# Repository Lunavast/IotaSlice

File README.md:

IotaSlice
===========

Iota is my approach at a little powder based 3D printer.

IotaSlice is a crude pre-alpha version of software the slices
3DS formatted 3D models into bitmap slices. Every pixel then
corresponds to the ink fired from a nozzle of the 3D printer.

The Iota firmware includes a minimal interpreter that reads
files in a propritary language from SD card and creates the
appropriate signals for all steppers and the ink shield output
of the Iota machine, much like G-Code in the early days of
CNC machines.

Iota Slice uses OpenGL to create 2D surfaces out of 3D shapes.
Slices have a real height. They are not just 2D cuts through
the model, but real 3D slices of a give thinkness, projected
onto a 2D surface. This method may capture fine details that
may otherwise be lost.

Iota Slice has some crude ideas of a shell, creating different
ink densities around the model as opposed to the inside. There
are some first hooks to implement vertex-based color 
gradiations, but the 3DS interface is not yet implemented.
The next version will implement full color based on texture 
mapping.

Also, at some point, the entire code will have to be 
reorganized and cleaned and wrapped into a nice UI. Until
then, this code is purely educational for the brave.

 Matthias

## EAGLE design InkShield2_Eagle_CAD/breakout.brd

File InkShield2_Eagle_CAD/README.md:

InkShield2
============

This board has been tested. It works quite well.

Periperials required are Polulo stepper drivers for
X, Y, Z1, and Z2, four endstops (optical gates),
an HP ink head, and a four-line I2C display with
four push buttons for menu selection.

Power supply is via a regular PC power brick
that is siply plugged into the shield. The voltage
needed for the Arduino Mega, all steppers, the SD
card connector, and the Ink Head are all taken 
from or generated from the PC power supply.

This is my original setup:

 https://www.youtube.com/watch?v=zV6xfxpeGGE

 Matthias

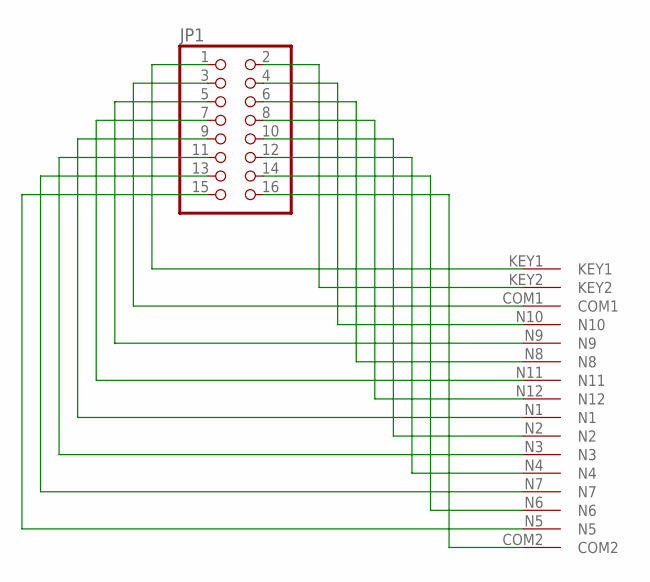
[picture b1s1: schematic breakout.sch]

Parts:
JP1: PINHD-2X8; 2X08
U$1: CON_16X1

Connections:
unnamed: JP1.1, U$1.KEY1
unnamed: JP1.2, U$1.KEY2
unnamed: JP1.3, U$1.COM1
unnamed: JP1.4, U$1.N10
unnamed: JP1.5, U$1.N9
unnamed: JP1.6, U$1.N8
unnamed: JP1.7, U$1.N11
unnamed: JP1.8, U$1.N12
unnamed: JP1.9, U$1.N1
unnamed: JP1.10, U$1.N2
unnamed: JP1.11, U$1.N3
unnamed: JP1.12, U$1.N4
unnamed: JP1.13, U$1.N7
unnamed: JP1.14, U$1.N6
unnamed: JP1.15, U$1.N5
unnamed: JP1.16, U$1.COM2

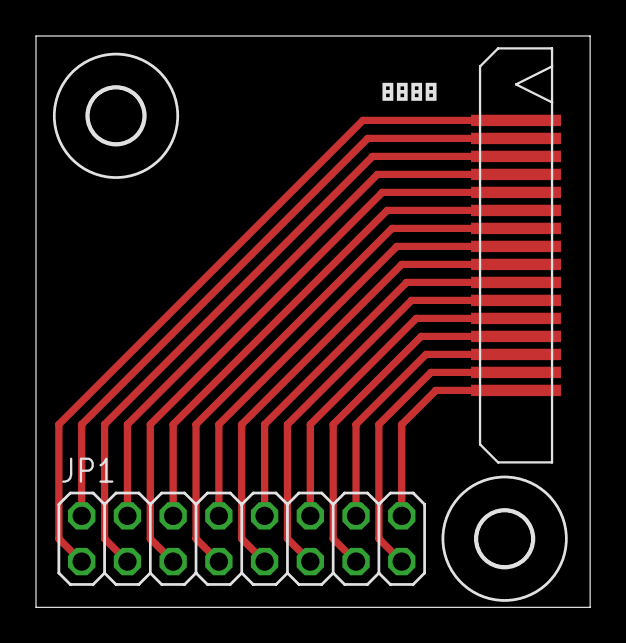
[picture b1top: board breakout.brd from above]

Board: 2 copper layers, 30.8 x 31.7 mm, 5 parts (0 on the bottom side), 16 nets.

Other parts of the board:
U$2: LP_NUMBER_SILK_TOP
U$3, U$4: 3,0

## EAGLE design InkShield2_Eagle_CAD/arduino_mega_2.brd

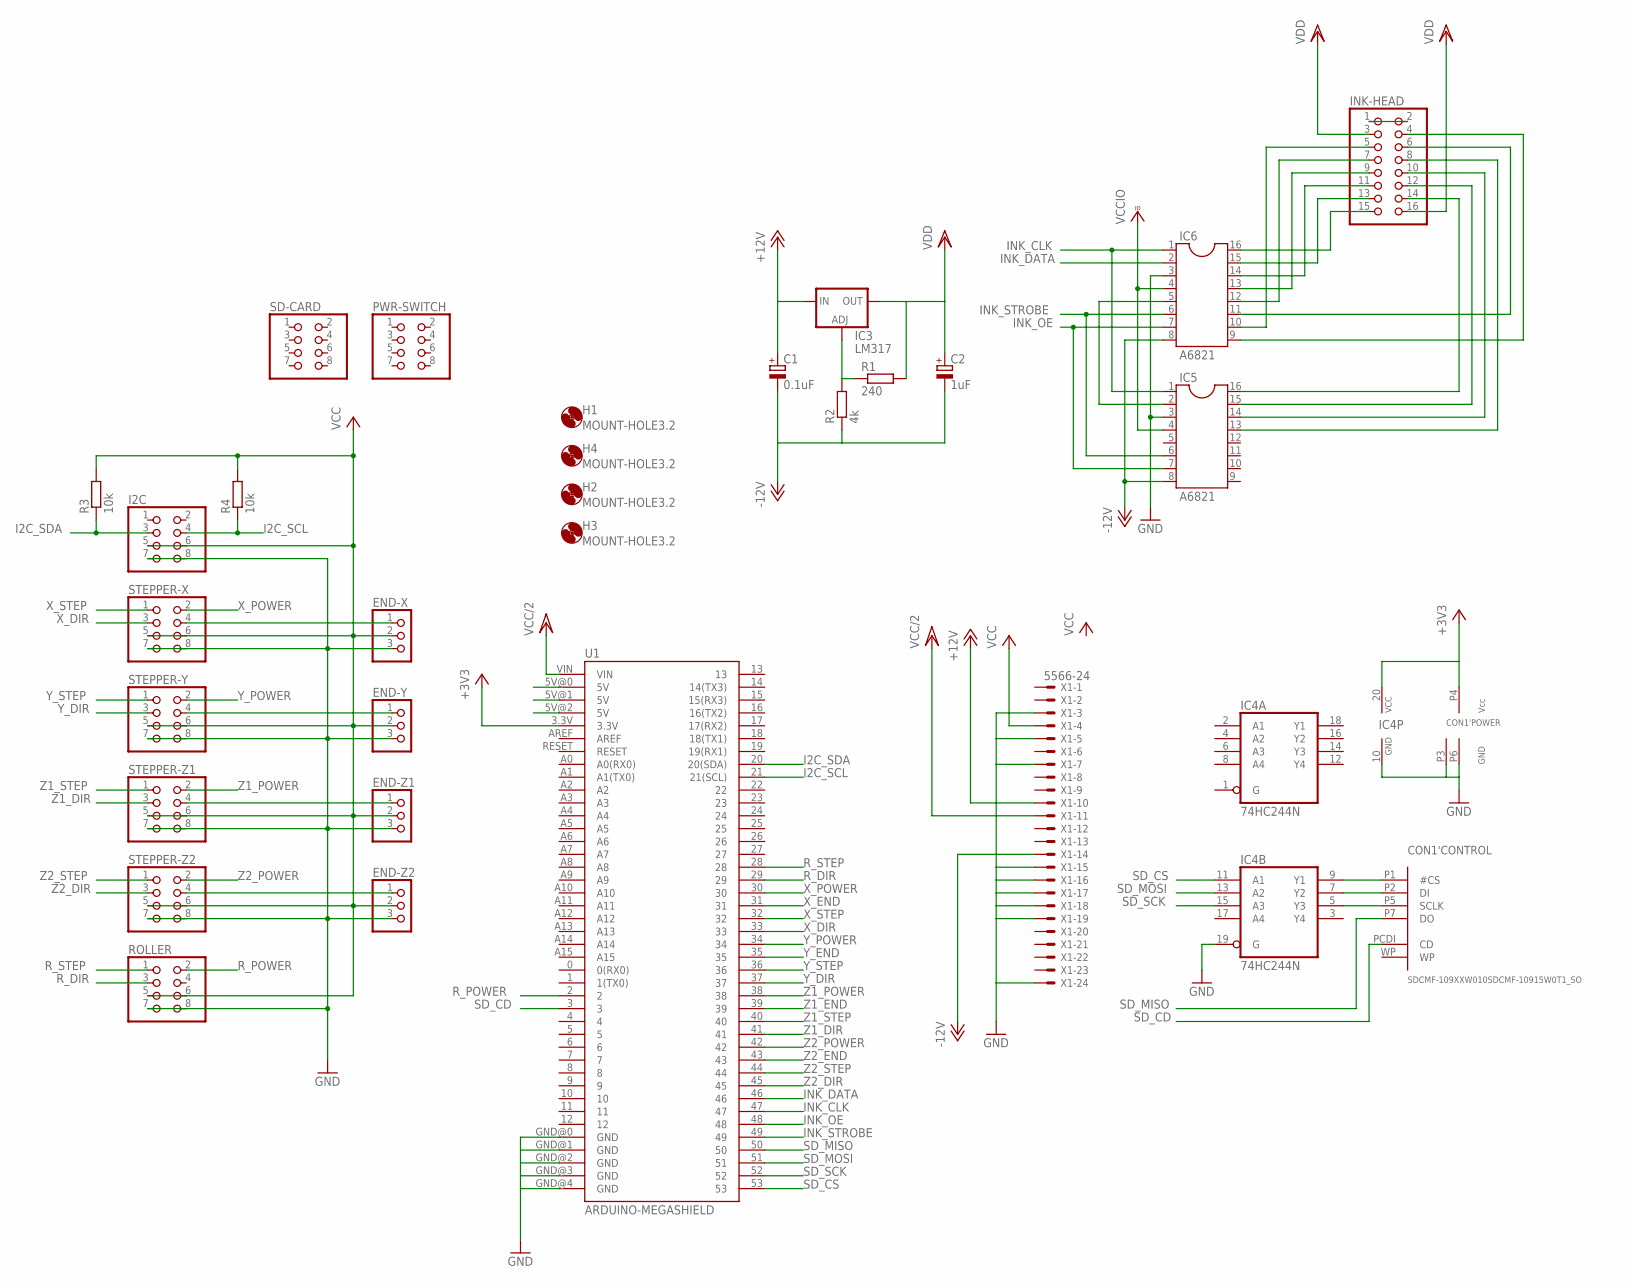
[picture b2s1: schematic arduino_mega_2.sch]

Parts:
C1: 0.1uF; E2-5
C2: 1uF; E2-5
CON1: SDCMF-109XXW010SDCMF-10915W0T1_SO; SDCMF-10915W0T1
END-X: PINHD-1X3; 1X03
END-Y: PINHD-1X3; 1X03
END-Z1, END-Z2: PINHD-1X3; 1X03
H1, H2, H3, H4: MOUNT-HOLE3.2; 3,2
I2C: PINHD-2X4; 2X04
IC3: LM317; 317TL
IC4: 74HC244N; DIL20
IC5, IC6: A6821; DIL16
INK-HEAD: PINHD-2X8; 2X08
PWR-SWITCH: PINHD-2X4; 2X04
R1: 240; 0207/10
R2: 4k; 0207/10
R3, R4: 10k; 0204/7
ROLLER: PINHD-2X4; 2X04
SD-CARD: PINHD-2X4; 2X04
STEPPER-X: PINHD-2X4; 2X04
STEPPER-Y: PINHD-2X4; 2X04
STEPPER-Z1, STEPPER-Z2: PINHD-2X4; 2X04
U1: ARDUINO-MEGASHIELD; ARDUINO_MEGA_SHIELD
X1: 5566-24

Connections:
+3V3: CON1.P4 (VCC), IC4.20 (VCC), U1.3.3V
+12V: C1.+, IC3.3 (IN), X1.10
-12V: C1.-, C2.-, IC5.8, IC6.8, R2.1, X1.14
GND: CON1.P3 (GND), CON1.P6 (GND), END-X.3, END-Y.3, END-Z1.3, END-Z2.3, I2C.7, I2C.8, IC4.10 (GND), IC4.19 (G), IC5.3, IC6.3, ROLLER.7, ROLLER.8, STEPPER-X.7, STEPPER-X.8, STEPPER-Y.7, STEPPER-Y.8, STEPPER-Z1.7, STEPPER-Z1.8, STEPPER-Z2.7, STEPPER-Z2.8, U1.GND@0 (GND), U1.GND@1 (GND), U1.GND@2 (GND), U1.GND@3 (GND), U1.GND@4 (GND), X1.3, X1.5, X1.7, X1.15, X1.16, X1.17, X1.18, X1.19, X1.24
I2C_SCL: I2C.4, R4.1, U1.21 (21(SCL))
I2C_SDA: I2C.3, R3.1, U1.20 (20(SDA))
INK_CLK: IC5.1, IC6.1, U1.47
INK_DATA: IC6.2, U1.46
INK_OE: IC5.7, IC6.7, U1.48
INK_STROBE: IC5.6, IC6.6, U1.49
unnamed: CON1.P1 (#CS), IC4.9 (Y1)
unnamed: CON1.P5 (SCLK), IC4.5 (Y3)
unnamed: CON1.P2 (DI), IC4.7 (Y2)
unnamed: INK-HEAD.1, INK-HEAD.2
unnamed: IC5.16, INK-HEAD.14
unnamed: IC5.15, INK-HEAD.12
unnamed: IC5.14, INK-HEAD.10
unnamed: IC5.13, INK-HEAD.8
unnamed: IC6.11, INK-HEAD.6
unnamed: IC6.9, INK-HEAD.4
unnamed: IC6.16, INK-HEAD.15
unnamed: IC6.15, INK-HEAD.13
unnamed: IC6.14, INK-HEAD.11
unnamed: IC6.13, INK-HEAD.9
unnamed: IC6.12, INK-HEAD.7
unnamed: IC6.10, INK-HEAD.5
unnamed: IC5.2, IC6.5
unnamed: IC3.1 (ADJ), R1.1, R2.2
R_DIR: ROLLER.3, U1.29
R_POWER: ROLLER.2, U1.2
R_STEP: ROLLER.1, U1.28
SD_CD: CON1.PCDI (CD), U1.3
SD_CS: IC4.11 (A1), U1.53
SD_MISO: CON1.P7 (DO), U1.50
SD_MOSI: IC4.13 (A2), U1.51
SD_SCK: IC4.15 (A3), U1.52
VCC: END-X.2, END-Y.2, END-Z1.2, END-Z2.2, I2C.5, I2C.6, R3.2, R4.2, ROLLER.5, ROLLER.6, STEPPER-X.5, STEPPER-X.6, STEPPER-Y.5, STEPPER-Y.6, STEPPER-Z1.5, STEPPER-Z1.6, STEPPER-Z2.5, STEPPER-Z2.6, X1.4
VCC/2: U1.VIN, X1.11
VCCIO: IC5.4, IC6.4, U1.5V@0 (5V), U1.5V@1 (5V), U1.5V@2 (5V)
VDD: C2.+, IC3.2 (OUT), INK-HEAD.3, INK-HEAD.16, R1.2
X_DIR: STEPPER-X.3, U1.33
X_END: END-X.1, STEPPER-X.4, U1.31
X_POWER: STEPPER-X.2, U1.30
X_STEP: STEPPER-X.1, U1.32
Y_DIR: STEPPER-Y.3, U1.37
Y_END: END-Y.1, STEPPER-Y.4, U1.35
Y_POWER: STEPPER-Y.2, U1.34
Y_STEP: STEPPER-Y.1, U1.36
Z1_DIR: STEPPER-Z1.3, U1.41
Z1_END: END-Z1.1, STEPPER-Z1.4, U1.39
Z1_POWER: STEPPER-Z1.2, U1.38
Z1_STEP: STEPPER-Z1.1, U1.40
Z2_DIR: STEPPER-Z2.3, U1.45
Z2_END: END-Z2.1, STEPPER-Z2.4, U1.43
Z2_POWER: STEPPER-Z2.2, U1.42
Z2_STEP: STEPPER-Z2.1, U1.44

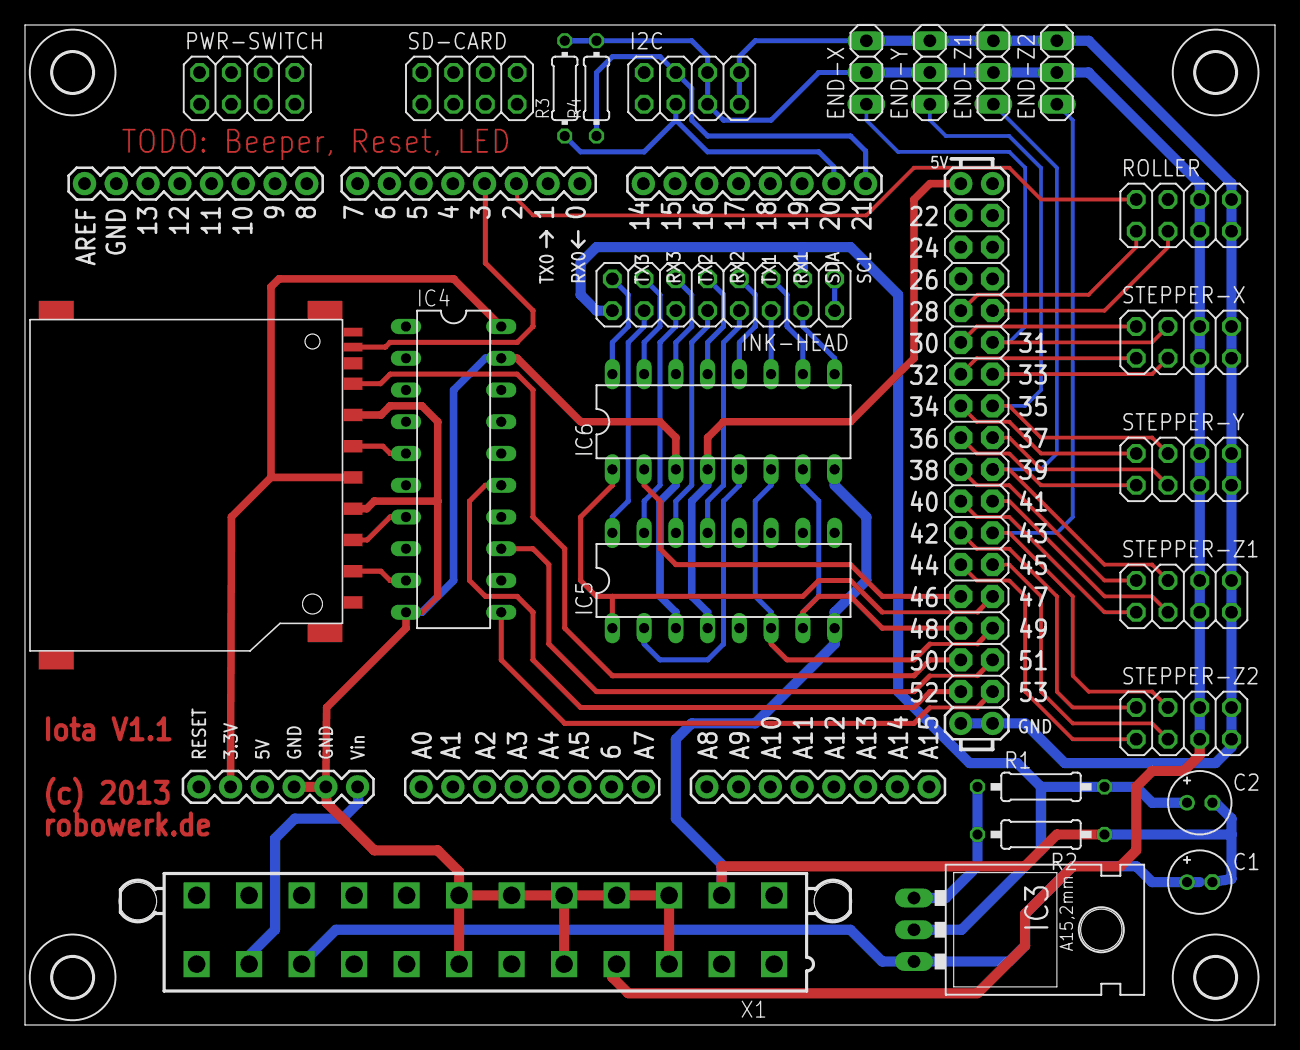
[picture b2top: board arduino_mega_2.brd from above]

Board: 2 copper layers, 100.0 x 80.0 mm, 30 parts (0 on the bottom side), 56 nets.

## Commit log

2015-02-26 Initial commit.
2015-02-26 Minor.
2015-03-21 Moved IotaSlice from FLTK 3 (which is no longer supported) to FLTK 1, including precompiled binaries of the library.
2015-03-21 Added build pahse to copy FLTK frameworks into the final product.
2015-03-21 Added a monley as a test object.

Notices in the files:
InkShield2_Eagle_CAD/arduino_mega_2.brd:
(c) 2013
parts and their libraries:
SparkFun-Boards: Licensing: CC v3.0 Share-Alike You are welcome to use this library for commercial purposes.
